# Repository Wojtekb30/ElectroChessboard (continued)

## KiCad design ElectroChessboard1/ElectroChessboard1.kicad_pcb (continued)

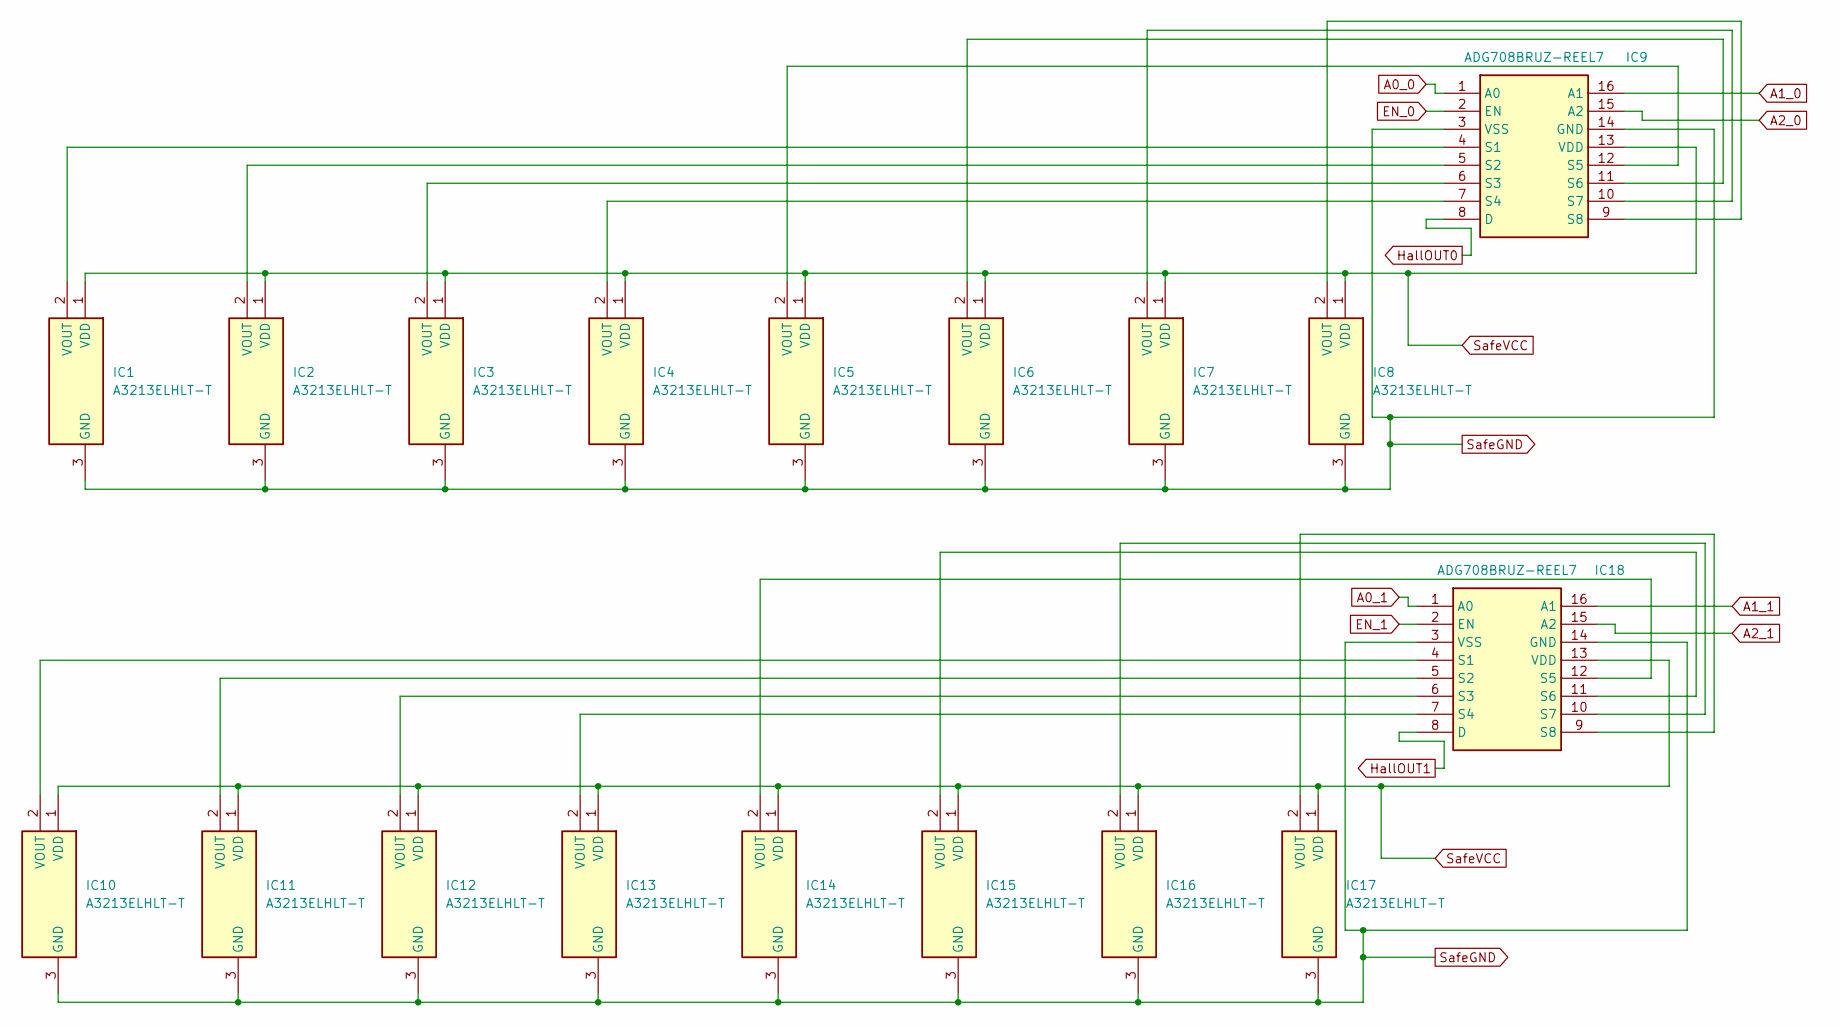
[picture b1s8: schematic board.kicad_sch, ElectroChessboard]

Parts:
IC1, IC2, IC3, IC4, IC5, IC6, IC7, IC8, IC10, IC11, IC12, IC13, IC14, IC15, IC16, IC17: A3213ELHLT-T; A3213ELHLTT; Mouser Part Number 250-A3213ELHLT-T
IC9, IC18: ADG708BRUZ-REEL7; SOP65P640X120-16N; Mouser Part Number 584-ADG708BRUZ-R7

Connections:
A0_0: IC9.1 (A0); also elsewhere on the board
A0_1: IC18.1 (A0); also elsewhere on the board
A1_0: IC9.16 (A1); also elsewhere on the board
A1_1: IC18.16 (A1); also elsewhere on the board
A2_0: IC9.15 (A2); also elsewhere on the board
A2_1: IC18.15 (A2); also elsewhere on the board
EN_0: IC9.2 (EN); also elsewhere on the board
EN_1: IC18.2 (EN); also elsewhere on the board
HallOUT0: IC9.8 (D); also elsewhere on the board
HallOUT1: IC18.8 (D); also elsewhere on the board
unnamed: IC1.2 (VOUT), IC9.4 (S1)
unnamed: IC2.2 (VOUT), IC9.5 (S2)
unnamed: IC3.2 (VOUT), IC9.6 (S3)
unnamed: IC4.2 (VOUT), IC9.7 (S4)
unnamed: IC5.2 (VOUT), IC9.12 (S5)
unnamed: IC6.2 (VOUT), IC9.11 (S6)
unnamed: IC7.2 (VOUT), IC9.10 (S7)
unnamed: IC8.2 (VOUT), IC9.9 (S8)
unnamed: IC10.2 (VOUT), IC18.4 (S1)
unnamed: IC11.2 (VOUT), IC18.5 (S2)
unnamed: IC12.2 (VOUT), IC18.6 (S3)
unnamed: IC13.2 (VOUT), IC18.7 (S4)
unnamed: IC14.2 (VOUT), IC18.12 (S5)
unnamed: IC15.2 (VOUT), IC18.11 (S6)
unnamed: IC16.2 (VOUT), IC18.10 (S7)
unnamed: IC17.2 (VOUT), IC18.9 (S8)
SafeGND: IC1.3 (GND), IC2.3 (GND), IC3.3 (GND), IC4.3 (GND), IC5.3 (GND), IC6.3 (GND), IC7.3 (GND), IC8.3 (GND), IC9.3 (VSS), IC9.14 (GND), IC10.3 (GND), IC11.3 (GND), IC12.3 (GND), IC13.3 (GND), IC14.3 (GND), IC15.3 (GND), IC16.3 (GND), IC17.3 (GND), IC18.3 (VSS), IC18.14 (GND); also elsewhere on the board
SafeVCC: IC1.1 (VDD), IC2.1 (VDD), IC3.1 (VDD), IC4.1 (VDD), IC5.1 (VDD), IC6.1 (VDD), IC7.1 (VDD), IC8.1 (VDD), IC9.13 (VDD), IC10.1 (VDD), IC11.1 (VDD), IC12.1 (VDD), IC13.1 (VDD), IC14.1 (VDD), IC15.1 (VDD), IC16.1 (VDD), IC17.1 (VDD), IC18.13 (VDD); also elsewhere on the board

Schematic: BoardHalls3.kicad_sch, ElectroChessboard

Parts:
IC37, IC38, IC39, IC40, IC41, IC42, IC43, IC44, IC45, IC46, IC47, IC48, IC49, IC50, IC51, IC52: A3213ELHLT-T; A3213ELHLTT; Mouser Part Number 250-A3213ELHLT-T
IC53, IC54: ADG708BRUZ-REEL7; SOP65P640X120-16N; Mouser Part Number 584-ADG708BRUZ-R7

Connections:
A0_4: IC54.1 (A0); also elsewhere on the board
A0_5: IC53.1 (A0); also elsewhere on the board
A1_4: IC54.16 (A1); also elsewhere on the board
A1_5: IC53.16 (A1); also elsewhere on the board
A2_4: IC54.15 (A2); also elsewhere on the board
A2_5: IC53.15 (A2); also elsewhere on the board
EN_4: IC54.2 (EN); also elsewhere on the board
EN_5: IC53.2 (EN); also elsewhere on the board
HallOUT4: IC54.8 (D); also elsewhere on the board
HallOUT5: IC53.8 (D); also elsewhere on the board
unnamed: IC37.2 (VOUT), IC53.4 (S1)
unnamed: IC38.2 (VOUT), IC54.4 (S1)
unnamed: IC39.2 (VOUT), IC53.5 (S2)
unnamed: IC40.2 (VOUT), IC54.5 (S2)
unnamed: IC41.2 (VOUT), IC53.6 (S3)
unnamed: IC42.2 (VOUT), IC54.6 (S3)
unnamed: IC43.2 (VOUT), IC53.7 (S4)
unnamed: IC44.2 (VOUT), IC54.7 (S4)
unnamed: IC45.2 (VOUT), IC53.12 (S5)
unnamed: IC46.2 (VOUT), IC54.12 (S5)
unnamed: IC47.2 (VOUT), IC53.11 (S6)
unnamed: IC48.2 (VOUT), IC54.11 (S6)
unnamed: IC49.2 (VOUT), IC53.10 (S7)
unnamed: IC50.2 (VOUT), IC54.10 (S7)
unnamed: IC51.2 (VOUT), IC53.9 (S8)
unnamed: IC52.2 (VOUT), IC54.9 (S8)
SafeGND: IC37.3 (GND), IC38.3 (GND), IC39.3 (GND), IC40.3 (GND), IC41.3 (GND), IC42.3 (GND), IC43.3 (GND), IC44.3 (GND), IC45.3 (GND), IC46.3 (GND), IC47.3 (GND), IC48.3 (GND), IC49.3 (GND), IC50.3 (GND), IC51.3 (GND), IC52.3 (GND), IC53.3 (VSS), IC53.14 (GND), IC54.3 (VSS), IC54.14 (GND); also elsewhere on the board
SafeVCC: IC37.1 (VDD), IC38.1 (VDD), IC39.1 (VDD), IC40.1 (VDD), IC41.1 (VDD), IC42.1 (VDD), IC43.1 (VDD), IC44.1 (VDD), IC45.1 (VDD), IC46.1 (VDD), IC47.1 (VDD), IC48.1 (VDD), IC49.1 (VDD), IC50.1 (VDD), IC51.1 (VDD), IC52.1 (VDD), IC53.13 (VDD), IC54.13 (VDD); also elsewhere on the board

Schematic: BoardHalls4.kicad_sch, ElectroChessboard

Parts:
IC55, IC56, IC57, IC58, IC59, IC60, IC61, IC62, IC63, IC64, IC65, IC66, IC67, IC68, IC69, IC70: A3213ELHLT-T; A3213ELHLTT; Mouser Part Number 250-A3213ELHLT-T
IC71, IC72: ADG708BRUZ-REEL7; SOP65P640X120-16N; Mouser Part Number 584-ADG708BRUZ-R7

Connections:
A0_6: IC72.1 (A0); also elsewhere on the board
A0_7: IC71.1 (A0); also elsewhere on the board
A1_6: IC72.16 (A1); also elsewhere on the board
A1_7: IC71.16 (A1); also elsewhere on the board
A2_6: IC72.15 (A2); also elsewhere on the board
A2_7: IC71.15 (A2); also elsewhere on the board
EN_6: IC72.2 (EN); also elsewhere on the board
EN_7: IC71.2 (EN); also elsewhere on the board
HallOUT6: IC72.8 (D); also elsewhere on the board
HallOUT7: IC71.8 (D); also elsewhere on the board
unnamed: IC55.2 (VOUT), IC71.4 (S1)
unnamed: IC56.2 (VOUT), IC72.4 (S1)
unnamed: IC57.2 (VOUT), IC71.5 (S2)
unnamed: IC58.2 (VOUT), IC72.5 (S2)
unnamed: IC59.2 (VOUT), IC71.6 (S3)
unnamed: IC60.2 (VOUT), IC72.6 (S3)
unnamed: IC61.2 (VOUT), IC71.7 (S4)
unnamed: IC62.2 (VOUT), IC72.7 (S4)
unnamed: IC63.2 (VOUT), IC71.12 (S5)
unnamed: IC64.2 (VOUT), IC72.12 (S5)
unnamed: IC65.2 (VOUT), IC71.11 (S6)
unnamed: IC66.2 (VOUT), IC72.11 (S6)
unnamed: IC67.2 (VOUT), IC71.10 (S7)
unnamed: IC68.2 (VOUT), IC72.10 (S7)
unnamed: IC69.2 (VOUT), IC71.9 (S8)
unnamed: IC70.2 (VOUT), IC72.9 (S8)
SafeGND: IC55.3 (GND), IC56.3 (GND), IC57.3 (GND), IC58.3 (GND), IC59.3 (GND), IC60.3 (GND), IC61.3 (GND), IC62.3 (GND), IC63.3 (GND), IC64.3 (GND), IC65.3 (GND), IC66.3 (GND), IC67.3 (GND), IC68.3 (GND), IC69.3 (GND), IC70.3 (GND), IC71.3 (VSS), IC71.14 (GND), IC72.3 (VSS), IC72.14 (GND); also elsewhere on the board
SafeVCC: IC55.1 (VDD), IC56.1 (VDD), IC57.1 (VDD), IC58.1 (VDD), IC59.1 (VDD), IC60.1 (VDD), IC61.1 (VDD), IC62.1 (VDD), IC63.1 (VDD), IC64.1 (VDD), IC65.1 (VDD), IC66.1 (VDD), IC67.1 (VDD), IC68.1 (VDD), IC69.1 (VDD), IC70.1 (VDD), IC71.13 (VDD), IC72.13 (VDD); also elsewhere on the board

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
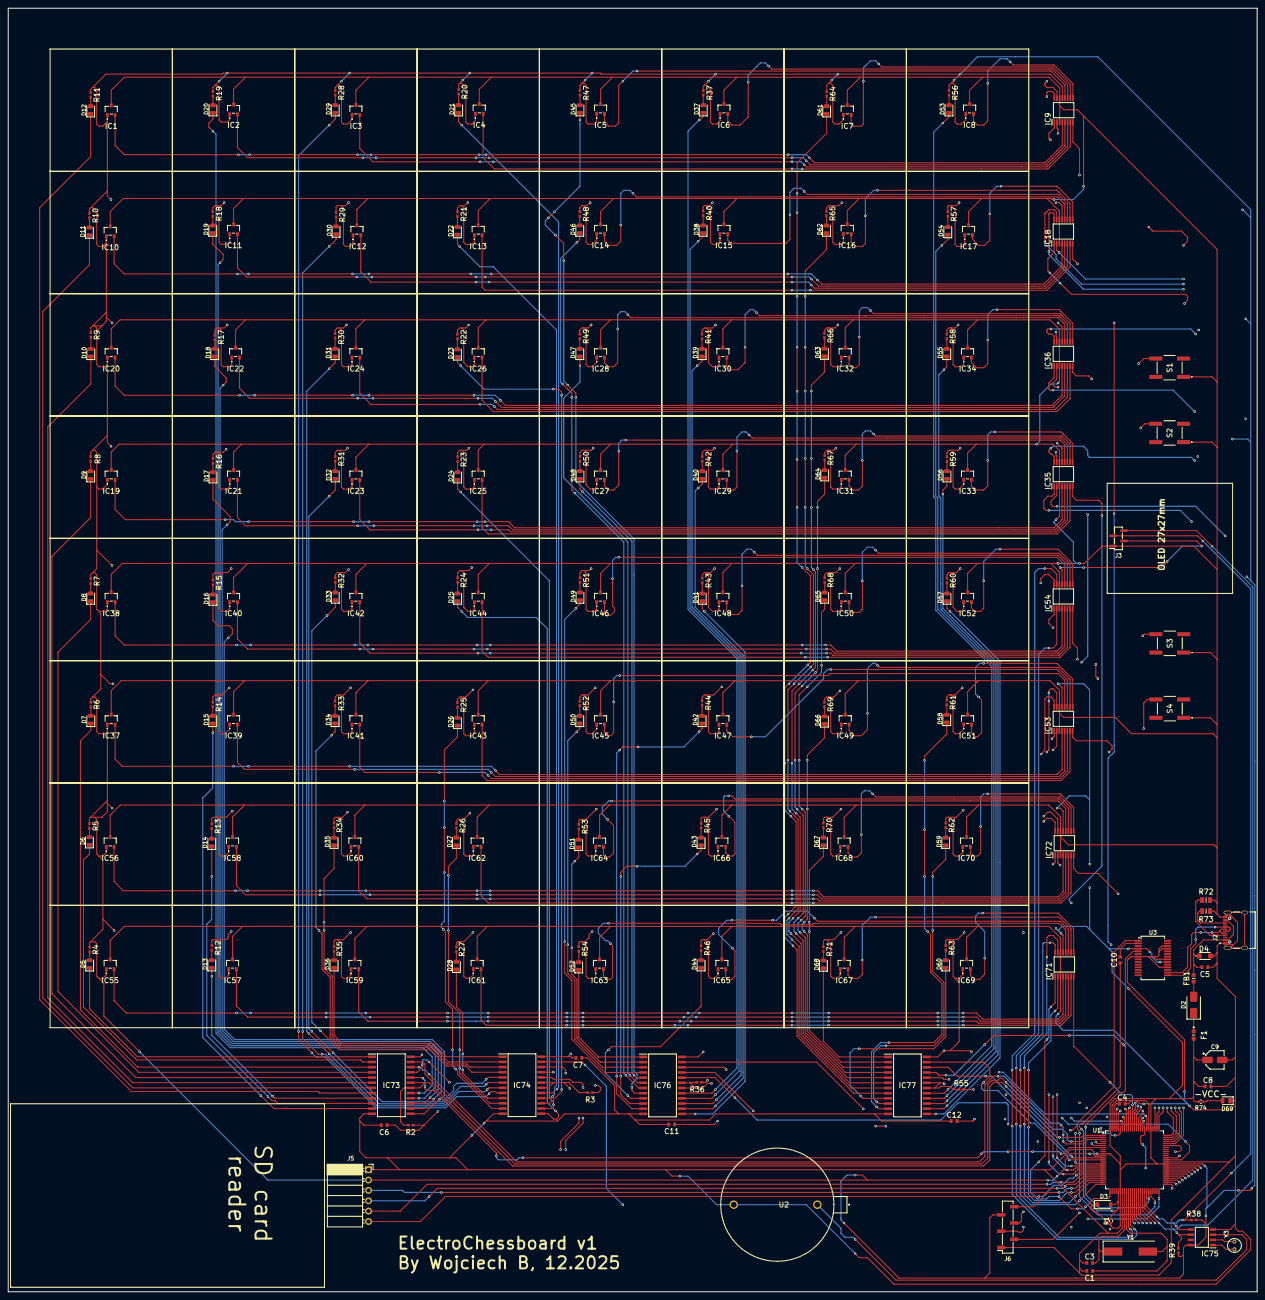
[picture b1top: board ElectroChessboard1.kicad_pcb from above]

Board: 4 copper layers, 306.2 x 314.8 mm, 245 parts (0 on the bottom side), 280 nets.

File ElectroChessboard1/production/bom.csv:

Designator,Footprint,Quantity,Value,LCSC Part #
"C1, C3",CAPC1608X90N,2,CL10C220JB8NNNC,
"C10, C11, C12, C4, C5, C6, C7, C8",CAPC1608X90N,8,CL10B104KC8NNNC,
C9,CP_Elec_4x5.4,1,C_Polarized,
"D10, D11, D12, D13, D14, D15, D16, D17, D18, D19, D20, D21, D22, D23, D24, D25, D26, D27, D28, D29, D30, D31, D32, D33, D34, D35, D36, D37, D38, D39, D40, D41, D42, D43, D44, D45, D46, D47, D48, D49, D5, D50, D51, D52, D53, D54, D55, D56, D57, D58, D59, D6, D60, D61, D62, D63, D64, D65, D66, D67, D68, D69, D7, D8, D9",0805,65,LED,
D2,D_SMA,1,SS12,
D3,D_SOD-123,1,1N4148,
D4,SOD123W,1,"PTVS5V0S1UTR,115",
F1,0603L050SLYR,1,0603L050SLYR,
FB1,BEADC1608X95N,1,GZ1608D601TF,
"IC1, IC10, IC11, IC12, IC13, IC14, IC15, IC16, IC17, IC19, IC2, IC20, IC21, IC22, IC23, IC24, IC25, IC26, IC27, IC28, IC29, IC3, IC30, IC31, IC32, IC33, IC34, IC37, IC38, IC39, IC4, IC40, IC41, IC42, IC43, IC44, IC45, IC46, IC47, IC48, IC49, IC5, IC50, IC51, IC52, IC55, IC56, IC57, IC58, IC59, IC6, IC60, IC61, IC62, IC63, IC64, IC65, IC66, IC67, IC68, IC69, IC7, IC70, IC8",A3213ELHLTT,64,A3213ELHLT-T,
"IC18, IC35, IC36, IC53, IC54, IC71, IC72, IC9",SOP65P640X120-16N,8,ADG708BRUZ-REEL7,
"IC73, IC74, IC76, IC77",SOIC127P1030X265-24N,4,CD74HC154M96,
IC75,SOIC127P600X175-8N,1,DS1307Z+T&R,
J2,HRO_TYPE-C-31-M-12,1,TYPE-C-31-M-12,
J3,PinSocket_1x04_P1.27mm_Vertical_SMD_Pin1Right,1,Conn_01x04_Pin,
J5,PinSocket_1x06_P2.54mm_Horizontal,1,Conn_01x06,
J6,PinSocket_1x06_P2.00mm_Vertical_SMD_Pin1Right,1,Conn_01x06,
"R1, R74",0402,2,R,
"R10, R11, R12, R13, R14, R15, R16, R17, R18, R19, R20, R21, R22, R23, R24, R25, R26, R27, R28, R29, R30, R31, R32, R33, R34, R35, R37, R4, R40, R41, R42, R43, R44, R45, R46, R47, R48, R49, R5, R50, R51, R52, R53, R54, R56, R57, R58, R59, R6, R60, R61, R62, R63, R64, R65, R66, R67, R68, R69, R7, R70, R71, R8, R9",RESC1005X40N,64,0402WGF1500TCE,
"R2, R3, R36, R55",RESC1005X40N,4,0402WGF1002TCE,
"R38, R39",RESC1005X40N,2,RC0402FR-074K7L,
"R72, R73",RESC2013X65N,2,0805W8F5101T5E,
"S1, S2, S3, S4",EVQ9P105M,4,EVQ-9P105M,
U1,TQFP-100_14x14mm_P0.5mm,1,ATmega2560-16A,
U2,1027,1,1027,
U3,SSOP-28_5.3x10.2mm_P0.65mm,1,FT232RL,
Y1,Crystal_SMD_HC49-SD,1,Crystal,
Y3,Crystal_C38-LF_D3.0mm_L8.0mm_Vertical,1,Crystal,

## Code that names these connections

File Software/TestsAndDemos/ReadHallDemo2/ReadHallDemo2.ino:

/*
  64-hall reader using 8 x ADG708BRUZ (one per row)
  readHall(x,y) -> x = column 0..7, y = row 0..7
  - Address pins for each row assumed in the order you gave (A0, A1, A2).
  - EN polarity: per ADG708 datasheet EN=1 enables a channel; EN=0 disables all.
  - Uses direct port access (PORTA, PORTC, PORTL, PORTH, PORTB).
*/

#include <Arduino.h>
#include <avr/io.h>

// ---------- configuration per your wiring (as provided) ----------
// EN pins (one ADG708 per row):
// Row 0 - PA3
// Row 1 - PA7
// Row 2 - PC0
// Row 3 - PC4
// Row 4 - PL0
// Row 5 - PL4
// Row 6 - PH3
// Row 7 - PB4

// Address pins for each row (listed in your message).
// Row 0: PA0, PA1, PA2        (A0,A1,A2)
// Row 1: PA4, PA5, PA6        (A0,A1,A2)
// Row 2: PC3, PC2, PC1        (A0,A1,A2)
// Row 3: PC7, PC6, PC5        (A0,A1,A2)
// Row 4: PL3, PL2, PL1        (A0,A1,A2)
// Row 5: PL7, PL6, PL5        (A0,A1,A2)
// Row 6: PH4, PH5, PH6        (A0,A1,A2)
// Row 7: PB7, PB6, PB5        (A0,A1,A2)

// ---------- helper inline functions ----------
static inline void setBit(volatile uint8_t &port, uint8_t bit, bool value) {
  if (value) port |= _BV(bit);
  else       port &= ~_BV(bit);
}

// Disable all EN lines (set EN = 0 = disabled)
void disableAllENs() {
  // PA3, PA7, PC0, PC4, PL0, PL4, PH3, PB4 -> clear their PORT bits
  PORTA &= ~(_BV(3) | _BV(7));
  PORTC &= ~(_BV(0) | _BV(4));
  PORTL &= ~(_BV(0) | _BV(4));
  PORTH &= ~_BV(3);
  PORTB &= ~_BV(4);
}

// Enable exactly one EN (EN = 1 enables). We first clear all ENs then set the one.
void enableRowEN(uint8_t row) {
  disableAllENs();
  switch (row) {
    case 0: PORTA |= _BV(3); break; // PA3
    case 1: PORTA |= _BV(7); break; // PA7
    case 2: PORTC |= _BV(0); break; // PC0
    case 3: PORTC |= _BV(4); break; // PC4
    case 4: PORTL |= _BV(0); break; // PL0
    case 5: PORTL |= _BV(4); break; // PL4
    case 6: PORTH |= _BV(3); break; // PH3
    case 7: PORTB |= _BV(4); break; // PB4
    default: break;
  }
}

// Set the three address pins (A0..A2) for a given row to value 'col' (0..7).
// Assumes the order you gave maps to A0, A1, A2 respectively.
void setAddressPins(uint8_t row, uint8_t col) {
  bool b0 = col & 0x1;
  bool b1 = col & 0x2;
  bool b2 = col & 0x4;

  switch (row) {
    case 0: // PA0, PA1, PA2
      setBit(PORTA, 0, b0);
      setBit(PORTA, 1, b1);
      setBit(PORTA, 2, b2);
      break;
    case 1: // PA4, PA5, PA6
      setBit(PORTA, 4, b0);
      setBit(PORTA, 5, b1);
      setBit(PORTA, 6, b2);
      break;
    case 2: // PC3, PC2, PC1
      setBit(PORTC, 3, b0);
      setBit(PORTC, 2, b1);
      setBit(PORTC, 1, b2);
      break;
    case 3: // PC7, PC6, PC5
      setBit(PORTC, 7, b0);
      setBit(PORTC, 6, b1);
      setBit(PORTC, 5, b2);
      break;
    case 4: // PL3, PL2, PL1
      setBit(PORTL, 3, b0);
      setBit(PORTL, 2, b1);
      setBit(PORTL, 1, b2);
      break;
    case 5: // PL7, PL6, PL5
      setBit(PORTL, 7, b0);
      setBit(PORTL, 6, b1);
      setBit(PORTL, 5, b2);
      break;
    case 6: // PH4, PH5, PH6
      setBit(PORTH, 4, b0);
      setBit(PORTH, 5, b1);
      setBit(PORTH, 6, b2);
      break;
    case 7: // PB7, PB6, PB5
      setBit(PORTB, 7, b0);
      setBit(PORTB, 6, b1);
      setBit(PORTB, 5, b2);
      break;
    default:
      break;
  }
}

// Call once in setup to configure DDRx for all used pins as outputs
void initMuxPins() {
  // Address pins and EN pins -> configure corresponding DDRx bits

  // PORTA pins used: PA0,PA1,PA2,PA3 (EN), PA4,PA5,PA6,PA7(EN)
  DDRA |= _BV(0)|_BV(1)|_BV(2)|_BV(3)|_BV(4)|_BV(5)|_BV(6)|_BV(7);

  // PORTC pins used: PC0(EN), PC1,PC2,PC3, PC4(EN), PC5,PC6,PC7
  DDRC |= _BV(0)|_BV(1)|_BV(2)|_BV(3)|_BV(4)|_BV(5)|_BV(6)|_BV(7);

  // PORTL pins used: PL0(EN), PL1,PL2,PL3, PL4(EN), PL5,PL6,PL7
  DDRL |= _BV(0)|_BV(1)|_BV(2)|_BV(3)|_BV(4)|_BV(5)|_BV(6)|_BV(7);

  // PORTH pins used: PH3(EN), PH4,PH5,PH6
  DDRH |= _BV(3)|_BV(4)|_BV(5)|_BV(6);

  // PORTB pins used: PB4(EN), PB5,PB6,PB7
  DDRB |= _BV(4)|_BV(5)|_BV(6)|_BV(7);

  // initial states: clear address pins and disable ENs
  PORTA &= ~(_BV(0)|_BV(1)|_BV(2)|_BV(3)|_BV(4)|_BV(5)|_BV(6)|_BV(7));
  PORTC &= ~(_BV(0)|_BV(1)|_BV(2)|_BV(3)|_BV(4)|_BV(5)|_BV(6)|_BV(7));
  PORTL &= ~(_BV(0)|_BV(1)|_BV(2)|_BV(3)|_BV(4)|_BV(5)|_BV(6)|_BV(7));
  PORTH &= ~(_BV(3)|_BV(4)|_BV(5)|_BV(6));
  PORTB &= ~(_BV(4)|_BV(5)|_BV(6)|_BV(7));
}

// ---------- the API function requested ----------
/*
  Read the hall sensor at column x (0..7), row y (0..7).
  Returns averaged ADC value (0..1023) on default Arduino ADC resolution (10-bit).
  Returns -1 if x or y out of range.
*/
int readHall(uint8_t x, uint8_t y) {
  if (x > 7 || y > 7) return -1;

  const uint8_t samples = 8;
  int sum = 0;

  // Ensure all ENs disabled while we change address lines:
  disableAllENs();

  // Set address bits for the targeted multiplexer (row)
  setAddressPins(y, x);

  // small settle after address change (depends on your hardware; increase if needed)
  delayMicroseconds(10);

  // Enable only the desired row
  enableRowEN(y);

  // allow mux + ADC to settle
  delayMicroseconds(80);

  // Read ADC on PFy (ADC channel y). Use analogRead(A0 + y).
  for (uint8_t i = 0; i < samples; ++i) {
    sum += analogRead(A0 + y);
    delayMicroseconds(15); // tiny gap between samples
  }

  // Optionally disable row again to avoid leakage/ghosting
  disableAllENs();

  return sum / samples;
}

// ---------- example usage ----------


// Array of Enable Pins for the 4 Demuxes
const int LEDenPins[] = {4, 5, 66, 67}; 

// 2D Array for Address Pins: [Demux Number][A0, A1, A2, A3]
const int LEDaddrPins[4][4] = {
  {0, 1, 2, 3},     // Demux 0: PE0, PE1, PE4, PE5
  {38, 39, 40, 41}, // Demux 1: PD7, PG2, PG1, PG0
  {68, 69, 18, 14}, // Demux 2: PK6, PK7, PD3, PJ1
  {16, 17, 19, 15}  // Demux 3: PH1, PH0, PD2, PJ0
};

/**
 * Setup all LEDs before operation
 */
void LEDsetup() {
  //Initialize all Enable pins to HIGH (Disabled) first
  for (int i = 0; i < 4; i++) {
    digitalWrite(LEDenPins[i], HIGH);
    pinMode(LEDenPins[i], OUTPUT);
    
    //Initialize Address pins as OUTPUT
    for (int j = 0; j < 4; j++) {
      pinMode(LEDaddrPins[i][j], OUTPUT);
    }
  }
}

/**
 * The unified control function
 * @param x       X (0-7)
 * @param y       Y (0-7)
 * @param status  ON or OFF
 */
void setLED(int x, int y, bool status, bool disableOther = true) {
  y=7-y;
  //Logic: Map x,y to 1 of 4 demuxes and 1 of 16 pins
  int demuxIndex = x / 2;
  int pinAddress = (x % 2) * 8 + y;

  if (disableOther) {
  for (int i = 0; i < 4; i++) {
    digitalWrite(LEDenPins[i], HIGH);
  }}

  if (status) {
    //1. Set the 4-bit address on the specific demux pins
    for (int i = 0; i < 4; i++) {
      digitalWrite(LEDaddrPins[demuxIndex][i], (pinAddress >> i) & 0x01);
    }
    //2. Enable only that demux
    digitalWrite(LEDenPins[demuxIndex], LOW);
  }
}



#include <SoftwareSerial.h> 
SoftwareSerial MyFix(10, 19);

void setup() {
  LEDsetup();
  MyFix.begin(9600); 
  initMuxPins();
  delay(200);
  MyFix.println(F("64-hall reader ready"));
}

void loop() {
  // Example: sweep all sensors once and print
  for (uint8_t r = 0; r < 8; ++r) {
    for (uint8_t c = 0; c < 8; ++c) {
      int v = readHall(c, r);
      MyFix.print(v);
      MyFix.print('\t');
      if (v==0 && c<=5) {
        setLED(c,r,true, 1);
      }
      //else if (v>1 && c<=5) {
      //  setLED(c,r,false, false);
      //}
    }
    MyFix.println();
  }
  delay(500);
  MyFix.println("---");
}

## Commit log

2025-11-09 New project
    Created new, blank project in KiCad for the device
2025-11-11 Start + Halls
    Created base + placed all hall sensors
2025-11-12 LEDs added
    Wired Hall sensors and LEDs
2025-11-23 Added but not connected yet SD Card pins and RTC
    .
2025-11-25 Schematic practically done (V0)
    Only requires pin verification and setting footprints.
    PDFs and image added in this commit all come from arduino.cc and microchip.com
2025-12-10 Corrected footprints 1
    Chosen footprints for JLCPCB
    I may add USB insterface chip
2025-12-10 Added FT232RL
    Ready for PCB design
2025-12-10 JLCPCB Design Rules import
    .
2025-12-10 Chessboard layout
    drawn with silkscreen
2025-12-10 Hall detectors on chessboard
    I put them
2025-12-10 Hall sensors in middle of fields
    .
2025-12-13 Added all LEDs
    Added missing 32 leds
2025-12-13 Chessboard done
    Other parts left to place. Also, I changed some wiring in schematic, changing what was connected to RX TX1
2025-12-13 Added oled
    .
2025-12-13 Fixed pins
    Now footprints of pins match
2025-12-13 Big part layout done
    Microcontroller, mux/demux layout and of course wiring left. Also changed footprint of the SD card module pins.
2025-12-13 Layout done
    Now wiring is left, and few parts that do not need specific placement
2025-12-14 USB-C
    Changed USB to USB-C and replaced wrong diode, only on schematic
2025-12-14 Updated PCB
    usb-c
2025-12-14 Chessboard GNDs wired
    Chessboard GNDs wired
2025-12-14 Rotated all LEDs on PCB 180 degrees
    .
2025-12-14 leds positioned
    .
2025-12-14 Wired demuxes to leds
    .
2025-12-14 Muxes and demuxes wired to halls and leds
    .
2025-12-14 Wired power, partially CPU too
    .
2025-12-15 4 layers
    Conversion to 4 layers
2025-12-16 Wired VCCs on the chessboard
    .
2025-12-16 Constrains fix
    .
2025-12-16 update
    .
2025-12-16 Major wiring done, only VCCs and GNDs left
    Major wiring done, only VCCs and GNDs left
2025-12-16 update
    27 wiring connections left to make
2025-12-16 Wiring done
    TODO: move silkscreen layers to safety, add power status LED
2025-12-16 Added power status LED
    TODO: Move silkscreen texts out of soldiermasks
2025-12-19 Corrected silkscreens
    .
2025-12-19 Production files
    For JLCPCB
2026-01-02 Corrected FT-232-RL UART wiring
    I wired RX-TX wrong, which made programming via USB not possible and UART available only with SoftwareSerial. Now I corrected that.
2026-01-03 Revert last commit
2026-01-03 Bootloader
    Custom bootloader
2026-01-03 New tests
    HALL and RTC
2026-01-03 3D models
    Of chessboard top
2026-01-04 C base for game AI
    C base for writing game AI
2026-01-05 Chess engine update
    .
2026-01-05 nowe modele 3d
2026-01-05 Add piece encoding
    Added comments to clarify piece encoding in the game.
2026-01-05 SDcardholder model fix
    It had a small defect earlier
2026-01-05 Create 16pieces1.stl
    for 3D printing
2026-01-06 Chess icons
    For printing and sticking onto pieces
2026-01-07 Update FinalProgram1.ino
    Basic game logic
2026-01-07 Update FinalProgram1.ino
    TODO for now: fix beating opponent's chess figures issues
2026-01-07 Update FinalProgram1.ino
    It works!
2026-01-10 Update FinalProgram1.ino
    Fixed capture detection logic
2026-01-10 Added game over
    GAME OVER: Checkmate or stalemate!
2026-01-11 Added SD card logging
    It's with RTC time
2026-01-11 SD card support fix
    Fixed SD card support
2026-01-11 Added OLED support
    v1 is in fact ready now
2026-01-11 Added soft reboot
    Watchdog-based, once game ends
